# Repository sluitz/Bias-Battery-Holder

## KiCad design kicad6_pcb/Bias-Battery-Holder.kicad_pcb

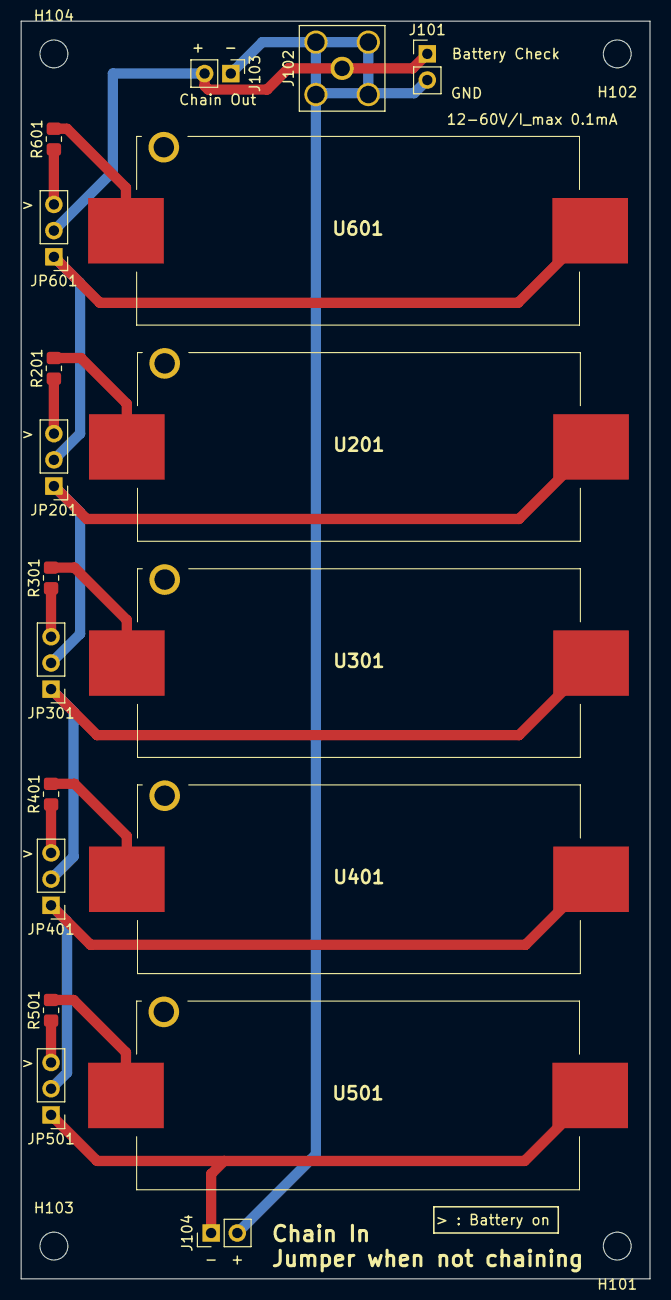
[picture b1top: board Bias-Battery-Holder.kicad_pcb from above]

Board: 2 copper layers, 61.0 x 121.9 mm, 23 parts (0 on the bottom side), 17 nets.

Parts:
H101, H102, H103, H104: MountingHole; MountingHole_2.7mm_M2.5
J101: V_Test; PinHeader_1x02_P2.54mm_Vertical
J102: Conn_Coaxial; SMA_Amphenol_132203-12_Horizontal
J103: Chain Out; PinHeader_1x02_P2.54mm_Vertical
J104: Chain In; PinHeader_1x02_P2.54mm_Vertical
JP201, JP301, JP401, JP501, JP601: Bypass; PinHeader_1x03_P2.54mm_Vertical
R201, R301, R401, R501, R601: 120k; R_0805_2012Metric_Pad1.20x1.40mm_HandSolder
U201, U301, U401, U501, U601: Keystone-1018-SMD; Keystone-1018

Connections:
/Battery unit1/V_batt-: JP301.1 (A), JP401.2 (C), U301.2 (-)
/Battery unit2/V_batt-: JP401.1 (A), JP501.2 (C), U401.2 (-)
/Battery unit3/V_batt-: J104.1, JP501.1 (A), U501.2 (-)
/Battery unit8/V_batt+12V: J101.1, J102.1 (In), J103.2, JP601.2 (C)
/Battery unit/V_batt+12V: JP201.2 (C), JP601.1 (A), U601.2 (-)
/Battery unit/V_batt-: JP201.1 (A), JP301.2 (C), U201.2 (-)
GND: J101.2, J102.2 (Ext), J103.1, J104.2
unnamed: JP201.3 (B), R201.1
unnamed: JP301.3 (B), R301.1
unnamed: JP401.3 (B), R401.1
unnamed: JP501.3 (B), R501.1
unnamed: JP601.3 (B), R601.1
unnamed: R201.2, U201.1 (+)
unnamed: R301.2, U301.1 (+)
unnamed: R401.2, U401.1 (+)
unnamed: R501.2, U501.1 (+)
unnamed: R601.2, U601.1 (+)
